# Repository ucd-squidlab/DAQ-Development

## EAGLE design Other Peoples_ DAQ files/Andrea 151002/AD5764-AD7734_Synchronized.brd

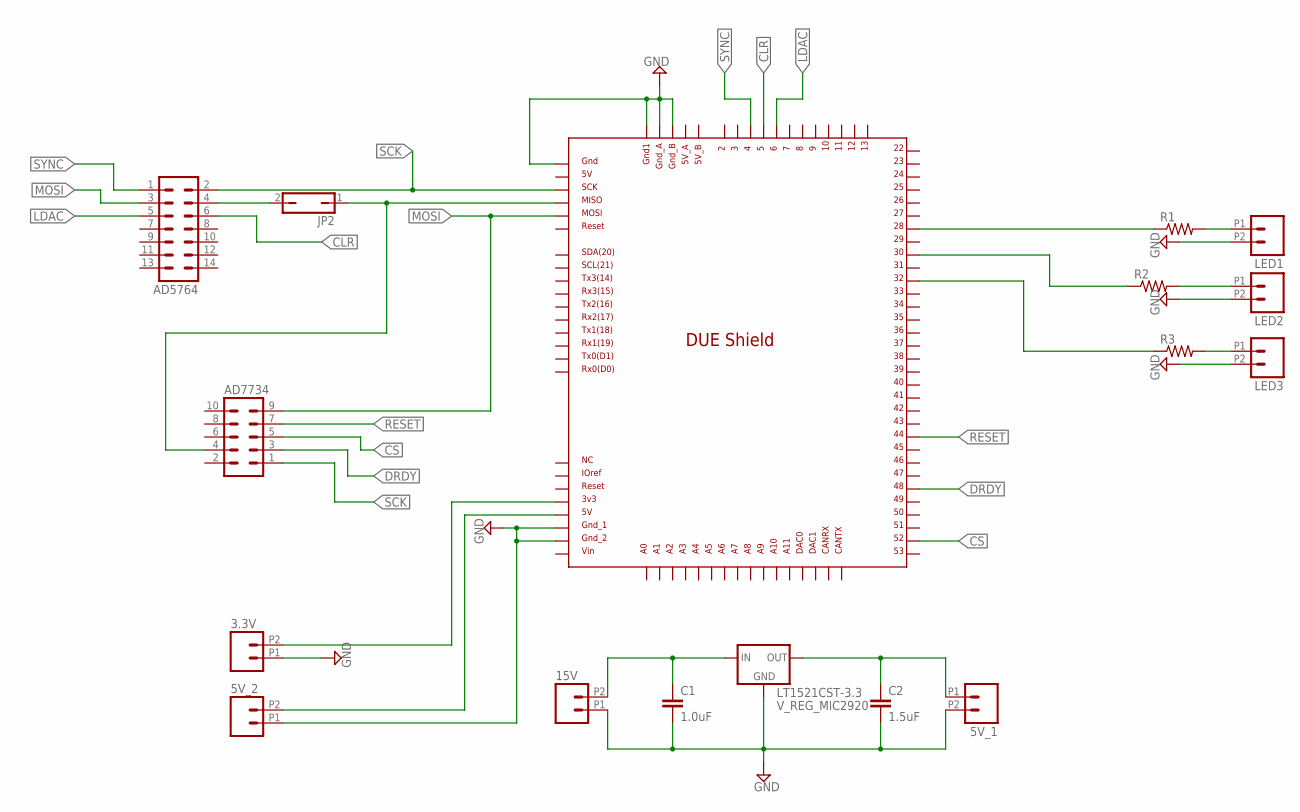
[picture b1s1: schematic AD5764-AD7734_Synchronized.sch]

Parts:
3.3V, 5V_1, 5V_2, 15V: M022.54MM_SCREWTERM; 1X02_2.54_SCREWTERM
AD5764: MA07-2
AD7734: MA05-2
C1: 1.0uF; 0603-CAP
C2: 1.5uF; 0603-CAP
JP2: JP1Q; JP1
LED1, LED2, LED3: M022.54MM_SCREWTERM; 1X02_2.54_SCREWTERM
LT1521CST-3.3: V_REG_MIC2920; SOT223
R1, R2, R3: R-US_R1206; R1206
U$2: DUE(REDUCED)

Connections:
CLR: AD5764.6, U$2.5
CS: AD7734.5, U$2.52
DRDY: AD7734.3, U$2.48
GND: 3.3V.P1 (1), 5V_1.P2 (2), 5V_2.P1 (1), 15V.P1 (1), C1.2, C2.2, LED1.P2 (2), LED2.P2 (2), LED3.P2 (2), LT1521CST-3.3.2 (GND), U$2.5V_ICSP, U$2.GND1, U$2.GND_1, U$2.GND_2, U$2.GND_A, U$2.GND_B
LDAC: AD5764.5, U$2.6
MOSI: AD5764.3, AD7734.9, U$2.MOSI_ICSP
unnamed: AD5764.4, JP2.2
unnamed: 3.3V.P2 (2), U$2.3V3
unnamed: 15V.P2 (2), C1.1, LT1521CST-3.3.1 (IN)
unnamed: 5V_1.P1 (1), C2.1, LT1521CST-3.3.3 (OUT)
unnamed: 5V_2.P2 (2), U$2.5V
unnamed: R2.1, U$2.30
unnamed: R3.1, U$2.32
unnamed: R1.1, U$2.28
unnamed: LED1.P1 (1), R1.2
unnamed: LED2.P1 (1), R2.2
unnamed: LED3.P1 (1), R3.2
unnamed: AD7734.4, JP2.1, U$2.MISO_ICSP
RESET: AD7734.7, U$2.44
SCK: AD5764.2, AD7734.1, U$2.SCK_ICSP
SYNC: AD5764.1, U$2.4

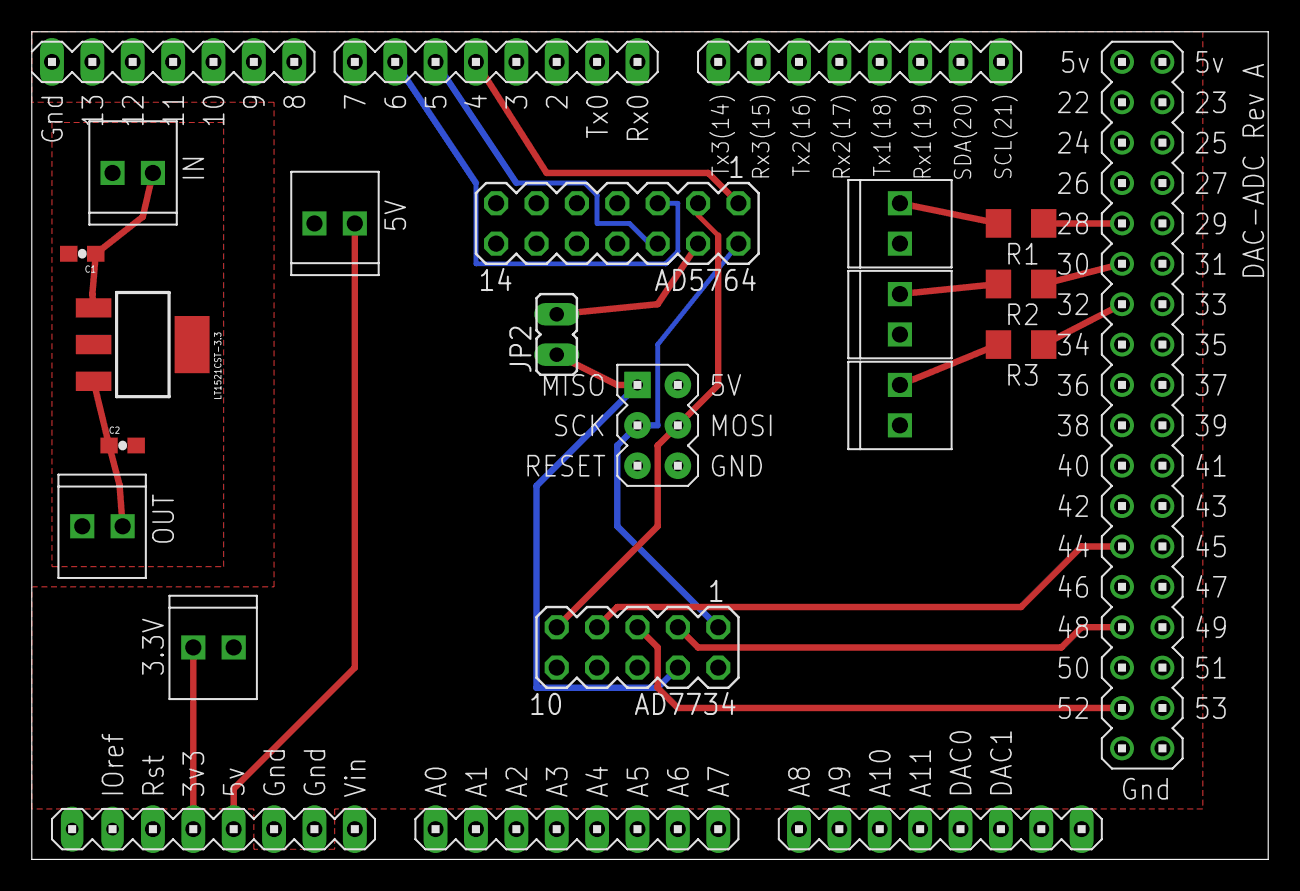
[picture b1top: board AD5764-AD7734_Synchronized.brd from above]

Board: 2 copper layers, 77.8 x 52.1 mm, 17 parts (0 on the bottom side), 21 nets.

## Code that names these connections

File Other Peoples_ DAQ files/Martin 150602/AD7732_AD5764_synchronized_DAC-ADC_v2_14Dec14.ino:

//Ardunio *DUE(*code for controlling EVAL-AD7732 ADC 
#include "SPI.h" // necessary library for SPI communication

int adc=52; //The SPI pin for the ADC
int dac=4;  //The SPI pin for the DAC
int ldac=6; //Load DAC pin for DAC. Make it LOW if not in use. 
int clr=5;  // Asynchronous clear pin for DAC. Make it HIGH if you are not using it
int reset=51; //Reset on ADC
int drdy=50; // Data is ready pin on ADC
int led=13;//Used for trouble shooting; connect an LED between pin 53 and GND\
int debug=10;

void setup()
{
  Serial.begin(115200);
  pinMode(ldac,OUTPUT);   
  digitalWrite(ldac,LOW); //Load DAC pin for DAC. Make it LOW if not in use. 
  pinMode(clr, OUTPUT);
  digitalWrite(clr,HIGH); // Asynchronous clear pin for DAC. Make it HIGH if you are not using it
  pinMode(reset, OUTPUT);
  pinMode(drdy, INPUT);  //Data ready pin for the ADC.  
  pinMode(led, OUTPUT);  //Used for blinking indicator LED

  digitalWrite(reset,HIGH);  digitalWrite(led,LOW); digitalWrite(reset,LOW);  digitalWrite(led,HIGH); delay(5);  digitalWrite(reset,HIGH);  digitalWrite(led,LOW);//Resets ADC on startup.  

  SPI.begin(adc); // wake up the SPI bus for ADC
  SPI.begin(dac); // wake up the SPI bus for ADC
  SPI.begin(debug); // wake up the SPI bus for ADC
  
  SPI.setBitOrder(adc,MSBFIRST); //correct order for AD7732.
  SPI.setBitOrder(dac,MSBFIRST); //correct order for AD5764.
  SPI.setBitOrder(debug,MSBFIRST); //correct order for AD5764.
    
  SPI.setClockDivider(adc,84);  //This can probably be sped up now that the rest of the code is better optimized. Limited by ADC
  SPI.setClockDivider(dac,84);  //This can probably be sped up now that the rest of the code is better optimized. Limited by ADC\
  SPI.setClockDivider(debug,84);  //This can probably be sped up now that the rest of the code is better optimized. Limited by ADC
  SPI.setDataMode(adc,SPI_MODE3); //This should be 3 for the AD7732
  SPI.setDataMode(dac,SPI_MODE1); //This should be 1 for the AD5764
  SPI.setDataMode(debug,SPI_MODE1); //This should be 1 for the AD5764
}

void blinker(int s){digitalWrite(led,HIGH);delay(s);digitalWrite(led,LOW);delay(s);}
void sos(){blinker(50);blinker(50);blinker(50);blinker(500);blinker(500);blinker(500);blinker(50);blinker(50);blinker(50);}

void waitDRDY() {while (digitalRead(drdy)==HIGH){}}

void resetADC() //Resets the ADC, and sets the range to default +-10 V 
{
  digitalWrite(led,HIGH);digitalWrite(reset,HIGH);digitalWrite(reset,LOW);digitalWrite(reset,HIGH);
  SPI.transfer(adc,0x28);
  SPI.transfer(adc,0);
  SPI.transfer(adc,0x2A);
  SPI.transfer(adc,0);
}

void talkADC(byte DB[7])
{
  int comm;
  comm=SPI.transfer(adc,DB[1]);
  Serial.println(comm);
  Serial.flush();
}

void writeADCConversionTime(byte DB[7])
{
  int adcChannel=DB[0]&3;
  byte cr;
  switch (adcChannel)
  {   
    case 1:
    SPI.transfer(adc,0x30);
    SPI.transfer(adc,DB[1]);
    delayMicroseconds(100);
    SPI.transfer(adc,0x70);
    cr=SPI.transfer(adc,0); //Read back the CT register
    Serial.write(cr);
    blinker(59);
    break;
    
    case 2:
    SPI.transfer(adc,0x32);
    SPI.transfer(adc,DB[1]);
    delayMicroseconds(100);
    SPI.transfer(adc,0x72);
    cr=SPI.transfer(adc,0); 
    Serial.write(cr);
    blinker(59);blinker(59);
    break;
    
    default:
    blinker(50);blinker(50);blinker(50);blinker(50);blinker(50);blinker(50);
    break;
}

}

void getSingleReading(int adcchan)
{Serial.flush();
  int statusbyte=0;
  byte o2;
  byte o3;
  int ovr;
  switch (adcchan)
  {
    case 0:
//    blinker(100);
    SPI.transfer(adc,0x38);
    SPI.transfer(adc,0x48);
    waitDRDY();
    SPI.transfer(adc,0x48);
    statusbyte=SPI.transfer(adc,0);
    o2=SPI.transfer(adc,0);
    o3=SPI.transfer(adc,0);
    ovr=statusbyte&1;
    switch (ovr)
    {
      case 0:
      Serial.write(o2);
      Serial.write(o3);
      break;
      
      case 1:
      Serial.write(byte(128));
      Serial.write(byte(0));
      break;   
    }
    break;
    
    case 1:
    SPI.transfer(adc,0x3A);
    SPI.transfer(adc,0x48);
    waitDRDY();
    SPI.transfer(adc,0x4A);
    statusbyte=SPI.transfer(adc,0);
    o2=SPI.transfer(adc,0);
    o3=SPI.transfer(adc,0);
    ovr=statusbyte&1;
    switch (ovr)
    {
      case 0:
      Serial.write(o2);
      Serial.write(o3);
      break;
      
      case 1:
      Serial.write(byte(128));
      Serial.write(byte(0));
      break;   
    }
    break; 
    
    default:
//    blinker(100);blinker(1000);blinker(100);blinker(100);
    break;
  }

}

void readADC(byte DB)
{
int adcChannel=DB&3;
switch (adcChannel)
{case 0:
break;
case 1:
getSingleReading(0);
break;
case 2:
getSingleReading(1);
break;
case 3:
getSingleReading(0);
delayMicroseconds(50);
getSingleReading(1);
break;
default:  
break;
}
}

int twoByteToInt(byte DB1,byte DB2) // This gives a 16 bit integer (between +/- 2^16)
{return ((int)((DB1<<24)| DB2))>>16;
}

int intToTwoByteDB1(int s) //needs 32bit style integer representation of actual 16 bit number
{return ((s>>8)&0xFF);}
int intToTwoByteDB2(int s)
{return (s&0xFF);}

void dacDataSend(int ch, byte DB1,byte DB2)
{SPI.transfer(dac,16+ch,SPI_CONTINUE);
SPI.transfer(dac,DB1,SPI_CONTINUE);
SPI.transfer(dac,DB2);}

void autoRamp(byte DB[7])
{
int v1=twoByteToInt(DB[1],DB[2]);
int v2=twoByteToInt(DB[3],DB[4]);
int nSteps=(DB[5]);
int b1;
int b2;
int dacChannel=(DB[0]>>2)&3;
for (int j=0; j<nSteps;j++)
{
b1=intToTwoByteDB1(v1+(v2-v1)*j/(nSteps-1));
b2=intToTwoByteDB2(v1+(v2-v1)*j/(nSteps-1));
dacDataSend(dacChannel,b1,b2);
delayMicroseconds(50);
readADC(DB[0]);
}

}


void writeDAC(byte DB[7])
{
int dacChannel=(DB[0]>>2)&3;
dacDataSend(dacChannel,DB[1],DB[2]);
}


void router(byte DB[7])
{
  Serial.flush();
  switch ((DB[0]>>4) & 15)//uses the first four bits of the first byte to choose what to do.  0000=0=read ADC: 0001=1=Write DAC; 0010=2=autoramp and acquire
  {
    case 0: // Read ADC 
    readADC(DB[0]);
    break;
    
    case 1: // Write DAC **IMPLEMENTED, WORKS
    writeDAC(DB);
    break;
    
    case 2: // Autoramp
    autoRamp(DB);
    break;

    case 3:
    resetADC();
    break;
    
    case 4:
    talkADC(DB);
    break;
    
    case 5: // Write conversion time registers
    writeADCConversionTime(DB);
    break;

    case 6: //Autocalibrate DAC gain and offset adjust NOT IMPLEMENTRED
//    dacAutoCal(DB);
    break;

    default:
    break;
}
}

void loop()
{
  byte bytes[7];
  while (Serial.available()<7) // wait until all data bytes are avaialable
  {
  }
if (Serial.available()) // wait until all three data bytes are avaialable
{
  digitalWrite(led,LOW);
  for (int i=0; i<7; i++) 
  {
    bytes[i] = Serial.read();
    SPI.transfer(debug,bytes[i]);
  }
Serial.flush();
}
router(bytes);
}

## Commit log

2021-11-12 Initial commit
    Contains code files that are actively being developed or would be useful as references.
2021-12-01 Add my work on Joe's code
    Add a folder with the AD7606 library derived from Joe's original library and a DAQ2.ino file derived from Joe's original DAQ.ino file
2021-12-03 Fix SPI syntax; test with 10kHz measurement
    Fixed the SPI syntax in the libraries. Pulled some of Cass's 10kHz experiment code to test whether the AD7606 library works. It does.
2021-12-03 Added the libraries back in
    Removed the libraries to get around a glitch in GitHub Desktop. Added them back now. Discovered that I needed to delete some .git folders from the libraries, and now it works.
2021-12-06 Update Python terminal code
    Update python terminal code to correctly convert the ADC output into a voltage
2021-12-10 Reorganize ADC readings code
    Move the code for ADC readings to its own separate function. Also add an LED toggle function.
2021-12-13 Add script to set DAC from MATLAB
    Add a test MATLAB script that sends a serial command from the host computer to the DAQ to set the DAC voltage. Also add a script that runs on the Teensy and checks the USB baud rate.
2021-12-17 Add ADC mode and register mode enabling functions
    Add functions to enable ADC mode or Register mode on the ADC. Also fix MATLAB script to read data properly over serial. Still not getting the right voltages from the ADC; turned on diagnostic mode to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
2022-01-31 Backup work
    Nothing was acting the way it was a week ago. Committing so that I can rewind and see whether the old code acts as expected
2022-01-31 Fix errors from last commit
    Fix SPI mode error from last commit. The diagnostic mode seems to be functioning as expected now.
2022-02-04 Update MATLAB app to interface with new DAQ server
    Update the MATLAB app to make it able to set and read voltages by communicating with the DAQ over USB serial. Also add some documentation to the DAQ server script describing what commands are current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
2022-02-11 MATLAB app can read ADC while scanning DAC
    Make MATLAB read the ADC while changing the DAC output.
2022-02-18 Fix Teensy serial commands
    Fix the Teensy code so that it can now receive all commands over serial; in the last couple commits, a bug prevented the processing of command IDs greater than 3.
    Rename files and update directory structure.
    Debug Python terminal script.
    Begin version numbering for Teensy.ino.
    Minor adjustments and improvements.
2022-02-25 Add slew rate limit, add ramp function
    Add slew rate limit to the Teensy.ino code. Expressed in micros./step. Step size is expressed in units of LSB. The slew rate can be different for each channel, but the step size is the same for all c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
    Also add ramp function to the Python terminal code. The function steps from a start to an end voltage and takes an ADC reading for each step.
2022-03-02 Allow reading from an arbitrary ADC channel
    Rewrote the ADC reading function so that it can retrieve the conversion result for any of the 8 channels. No support yet for readings from multiple different channels (each read must be performed sep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
2022-03-09 2D ramp function
    Add a 2D ramp function to the Python terminal application.
    Prepare AD7606 library for multi-channel readings: save the channel data to an array for later access. (Still need to implement a function for retrieving that data.)
2022-03-11 Redo last revisions and fix bugs
    Reduce number of serial write commands by combining data with padding before serial write in the SetDACVoltage function.
    Fix the 2D ramp again (my changes were lost before the last commit).
    Add optional settle time for ramp function; this waits after setting output voltage before taking a measurement.
    Fix bug in SetDACVoltage function in the Python terminal. The function was erroneously shifting the channel value left by two binary places.
2022-03-17 Split terminal and DAQ operations
    Separate the DAQ Python communication code from the Python terminal application. This will make it possible to design a GUI based on the DAQ operations. (This has not been tested.)
2022-03-17 Implement multi-channel ADC readings
    Test the last commit and resolve bugs. The code seems to run consistently now.
    Implement multi-channel ADC readings from Python. Turns out that it is possible to read the ADC conversion results multiple times after a single conversion.
2022-03-21 Capture noise spectral data
    Add DAQ ability to sample continuously for a period of time, and send results over serial
    Allow DAC to set all channels even with slew rate restrictions
    Add Python function to collect a continuous set of samples from the DAQ
    Modify Python _WaitForSerial to repeatedly check for more serial data before returning result
    Update Python Twos2Float function to accept NumPy arrays as well as scalars
    Modify Python terminal to close the serial port even when the program crashes
2022-03-21 Fix version number
    Fix version number
2022-03-23 Add ramp with dither, improve FFT
    Add a ramp function that uses dither (not tested yet)
    Add a GetConversionDataFast function in the AD7606 library which can get the conversion results from channel 0 much more quickly. This function does not process the data, and simply adds it to an arr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
    Add an FFT function to the Python daq module (originally, the FFT function was only in the Python terminal program)
    Fix a bug in the AD7606 library
    Add comments in various areas
    The FFT functionality is slow; not sure why. Also there are some issues with transferring data from the Teensy to the host computer - sometimes not all of the data gets transferred.
2022-04-01 Fix dither ramp plotting
    Fix plotting for dither ramp.
    Change daq.setup so that the default port is "COM7" if unspecified.
    Flush serial USB input and output before requesting data.
    If fast-sample data is missing some data, re-request the data up to a maximum number of retries until the transfer is successful.
    Add lots of comments.
2022-04-01 Add comments
    Add comments.
    Simplify the code that generates a list of frequencies in the Python terminal FFT function.
2022-04-06 Add default DAC wait time for GetPoint function
    Add a default wait time for the GetPoint function when it changes the DAC.
    Keep track of the current output voltage for each DAC channel. When updating the DAC, check whether it already has the desired voltage; if so, return. (Included an option to override this behavior.)
2022-05-04 Convert voltage range and step size
    The DAC has discrete output voltages and a limited range. For this commit I added a function to convert a voltage range (consisting of a start voltage, finish voltage, and number of steps) into a vol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
    I also added a function to convert a voltage value into an allowable DAC output voltage.
2022-05-04 Update .gitignore
    Ignore .pyc files. These are compiled Python binaries, and may be different on different systems.
2022-05-04 Delete old daq_terminal, rename new terminal to match
    Add some comments in the dac.py module. Delete the deprecated daq_terminal.py program from before March 16.
2022-05-06 Add comments. Add functions to calibrate DAC
    Add comments and clean up code.
    Add functions to the AD5764 library to allow adjustment of the fine gain and the offset.
    Calibrate the DAC in the Teensy.ino code. I used the Keithley 2000 to check the DAQ output, and adjusted the calibration to get the -9.99969 to +9.99969 range.
2022-05-13 Add comments
    Comments
2022-07-19 Create StephDAQWork
    GUI
2022-08-29 Create GUICurrentVersion
2022-09-17 quick hot changes
    removed the previous DAQ file because its name is a lie and it's messing up my mojo
    also added an OS-agnostic way to access user files
2022-09-17 magic of \t
2022-09-17 massive number of helper functions
    not sure if it needs "self" in all of them.
2022-09-17 made the helpers actually work.
2022-09-17 thankfully, this isn't necessary!
    but it will be later.
2022-09-17 fixed this too!
2022-09-17 adding QtUI file to git
2022-09-17 patching up the helpers
2022-09-17 fixing up the file output
2022-09-17 adding this in here to simply development
2022-09-17 finished basic kalamari framework
2022-09-21 added some more code for the actual kalamari loop
2022-09-25 midpoint save to transfer between computers
2022-09-26 maybe this will work!!!!
2022-09-28 nearly functional!
2022-09-28 gotta commit this i guess.
2022-12-21 Update DAQGraphing.py
    Start of the formatting code
2023-01-06 Update DAQGraphing.py
    Graphing Formatting
2023-01-06 external file save because martin said so
    untested as of commit
2023-01-06 undoing this to see if my login works
2023-03-01 Magnet GUI started, Lakeshore 331 datagather added
2023-03-02 Fixed the graphing!
2023-03-27 Data Management for Colormap Code
2023-04-05 added whitespace
2023-04-11 Began development of prologix-GPIB module
2023-04-17 Fixed RegEx in write method
2023-04-17 fixed file management
2023-04-19 MAC search function added
2023-04-26 Progress
2023-04-26 Fighting MacOS
2023-04-26 Removed getmac and finished read, write, and ask
2023-05-01 Plgxgpib is finally finishedgit add .
2023-05-01 Debugged instruments
2023-05-02 debugged instruments more

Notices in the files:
parts and their libraries:
SparkFun-Connectors: Licensing: Creative Commons ShareAlike 4.0 International - https://creativecommons.org/licenses/by-sa/4.0
